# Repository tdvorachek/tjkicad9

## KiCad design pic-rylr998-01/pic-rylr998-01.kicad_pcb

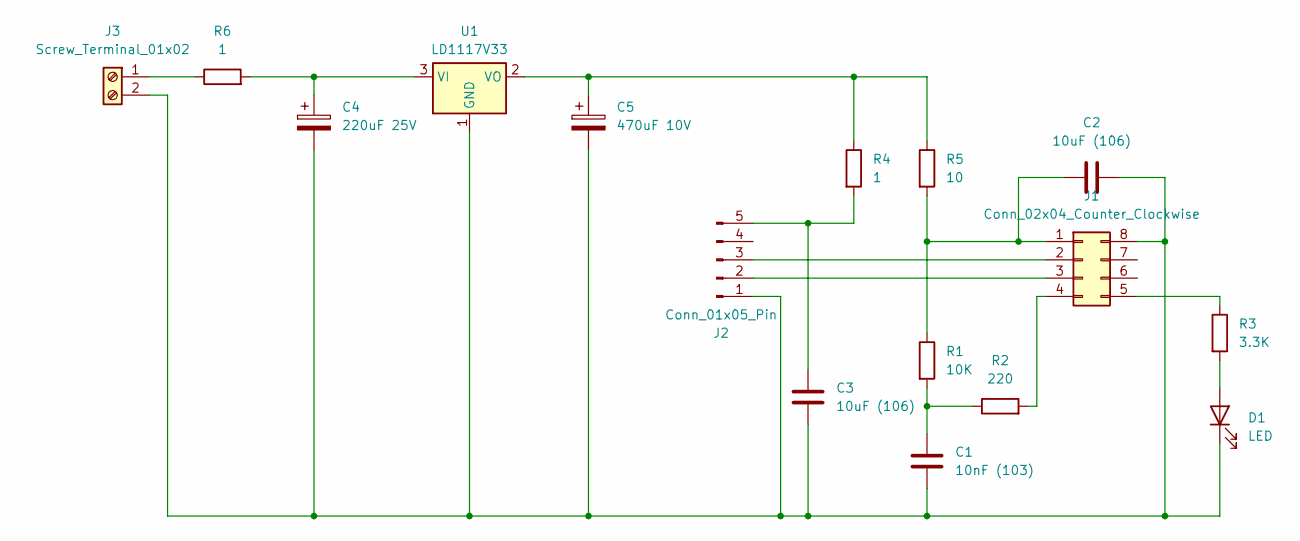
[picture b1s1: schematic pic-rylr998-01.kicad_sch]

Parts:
C1: 10nF (103); C_Disc_D8.0mm_W5.0mm_P5.00mm
C2, C3: 10uF (106); C_Disc_D8.0mm_W5.0mm_P5.00mm
C4: 220uF 25V; CP_Radial_D6.3mm_P2.50mm
C5: 470uF 10V; CP_Radial_D6.3mm_P2.50mm
D1: LED; LED_D5.0mm
J1: Conn_02x04_Counter_Clockwise; DIP-8_W7.62mm_Socket
J2: Conn_01x05_Pin; PinHeader_1x05_P2.54mm_Vertical
J3: Screw_Terminal_01x02; TerminalBlock_Phoenix_PT-1,5-2-5.0-H_1x02_P5.00mm_Horizontal
R1: 10K; R_Axial_DIN0207_L6.3mm_D2.5mm_P10.16mm_Horizontal
R2: 220; R_Axial_DIN0207_L6.3mm_D2.5mm_P2.54mm_Vertical
R3: 3.3K; R_Axial_DIN0207_L6.3mm_D2.5mm_P2.54mm_Vertical
R4, R6: 1; R_Axial_DIN0207_L6.3mm_D2.5mm_P2.54mm_Vertical
R5: 10; R_Axial_DIN0207_L6.3mm_D2.5mm_P2.54mm_Vertical
U1: LD1117V33; TO-220-3_Vertical

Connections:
unnamed: C1.1, R1.2, R2.1
unnamed: D1.2 (A), R3.2
unnamed: C1.2, C2.2, C3.2, C4.2, C5.2, D1.1 (K), J1.8, J2.1, J3.2, U1.1 (GND)
unnamed: C2.1, J1.1, R1.1, R5.2
unnamed: J1.2, J2.3
unnamed: J1.3, J2.2
unnamed: J1.4, R2.2
unnamed: J1.5, R3.1
unnamed: C3.1, J2.5, R4.2
unnamed: J3.1, R6.1
unnamed: C4.1, R6.2, U1.3 (VI)
unnamed: C5.1, R4.1, R5.1, U1.2 (VO)

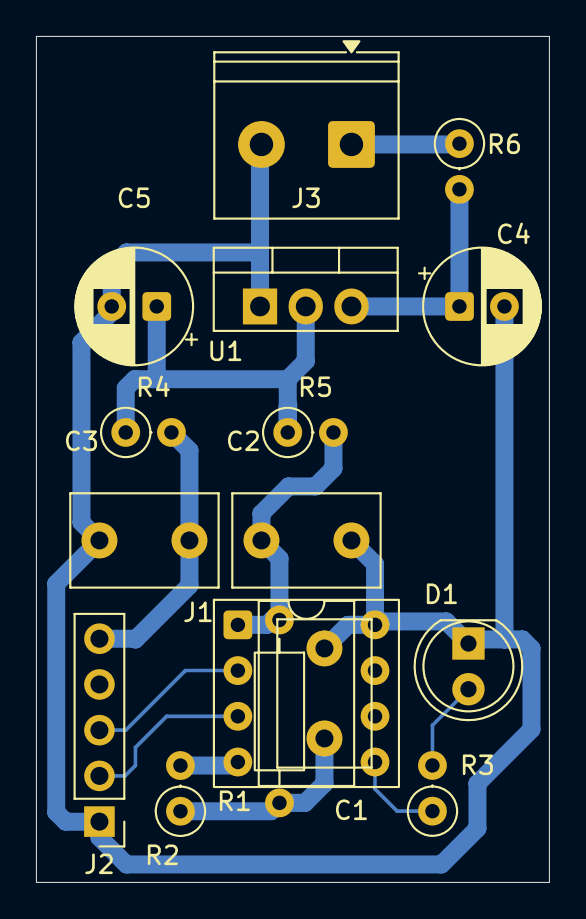
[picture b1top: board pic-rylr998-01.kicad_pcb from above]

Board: 2 copper layers, 28.5 x 47.0 mm, 16 parts (0 on the bottom side), 12 nets.

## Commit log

2025-11-04 added .gitignore file
2025-11-05 added pic-rylr998-01 research
2025-11-06 cleaned up board silkscreen and made all power supply related tracks 1 mm wide vs default 0.2 mm wide - the three signal lines RA2_LED RA4_PIC_RXD_RYLR998_TXD RA5_PIC_TXD_RYLR998_RXD tracks remain 0.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
2025-11-06 added pic-rylr998-01 pcb pdf pring and png snip after increasing track width of all power-related tracks
2025-11-06 created gerber and drill file plot files -and- zipped them -and- submitted to jlcpcb for manufacture and purchase
2025-11-06 added pic-rylr998-01 jlcpcb order details -and- jlcpcb instructions on how to generate the gerber and drillfile files in kicad 7 - these seem to work in kicad 9 since the order audit was approved
2025-11-06 added pic-rylr998-01 pic-rylr998-01-schematic-01-20251105.PNG and pic-rylr998-01-pcb-normal-01-20251105.PNG research
2025-11-07 renamed pic-rylr998-01 tjpic1-jlcpcb-pic-rylr998- files to pic-rylr998-01-jlcpcb- to be more meaningful
2025-11-11 added pic-rylr998-01 kicad-oshpark-OSH_Park-PCB-Generating_Gerbers-20251111.mhtml and kicad-oshpark-OSH_Park-PCB-Combining_KiCad_Drill_Files-Rheingold_Heavy-20251111.mhtml files
2025-11-13 renamed pic-rylr998-01 kicad-jlcpcb-How_to_generate_Gerber_and_Drill_files_in_KiCad_7-20251106.mhtml to eliminate the spaces within the file name
2025-11-13 moved pic-rylr998-01 kicad jlcpcb oshpark gerber drillfile instructions to dedicated kicad-pcb-fabricate-manufacture-instructions directory
2025-11-13 added tjcomponents1 research
